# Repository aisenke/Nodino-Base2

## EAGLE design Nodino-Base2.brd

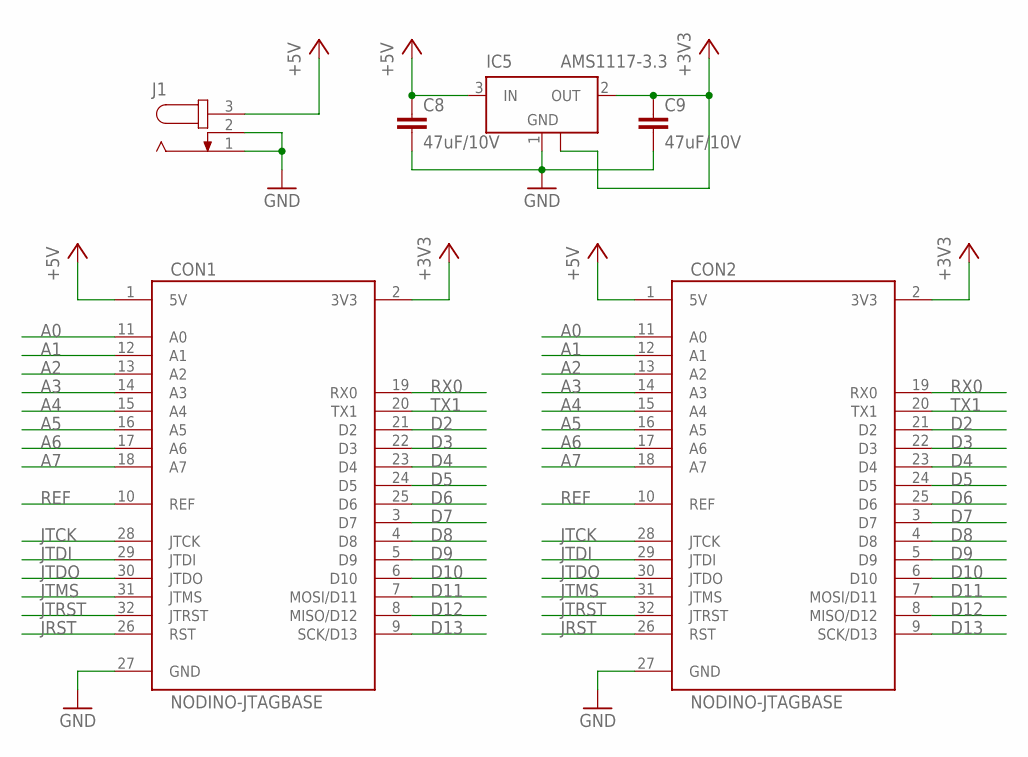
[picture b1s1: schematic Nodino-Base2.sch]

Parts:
C8, C9: 47uF/10V; C3225
CON1, CON2: NODINO-JTAGBASE; NODINO-JTAG-BASE
IC5: AMS1117-3.3; SOT223
J1: JACK-PLUG0; SPC4077

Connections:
+3V3: C9.1, CON1.2 (3V3), CON2.2 (3V3), IC5.2 (OUT), IC5.4 (GND)
+5V: C8.1, CON1.1 (5V), CON2.1 (5V), IC5.3 (IN), J1.3
A0: CON1.11 (A0), CON2.11 (A0)
A1: CON1.12 (A1), CON2.12 (A1)
A2: CON1.13 (A2), CON2.13 (A2)
A3: CON1.14 (A3), CON2.14 (A3)
A4: CON1.15 (A4), CON2.15 (A4)
A5: CON1.16 (A5), CON2.16 (A5)
A6: CON1.17 (A6), CON2.17 (A6)
A7: CON1.18 (A7), CON2.18 (A7)
D2: CON1.21 (D2), CON2.21 (D2)
D3: CON1.22 (D3), CON2.22 (D3)
D4: CON1.23 (D4), CON2.23 (D4)
D5: CON1.24 (D5), CON2.24 (D5)
D6: CON1.25 (D6), CON2.25 (D6)
D7: CON1.3 (D7), CON2.3 (D7)
D8: CON1.4 (D8), CON2.4 (D8)
D9: CON1.5 (D9), CON2.5 (D9)
D10: CON1.6 (D10), CON2.6 (D10)
D11: CON1.7 (MOSI/D11), CON2.7 (MOSI/D11)
D12: CON1.8 (MISO/D12), CON2.8 (MISO/D12)
D13: CON1.9 (SCK/D13), CON2.9 (SCK/D13)
GND: C8.2, C9.2, CON1.27 (GND), CON2.27 (GND), IC5.1 (GND), J1.1, J1.2
JRST: CON1.26 (RST), CON2.26 (RST)
JTCK: CON1.28 (JTCK), CON2.28 (JTCK)
JTDI: CON1.29 (JTDI), CON2.29 (JTDI)
JTDO: CON1.30 (JTDO), CON2.30 (JTDO)
JTMS: CON1.31 (JTMS), CON2.31 (JTMS)
JTRST: CON1.32 (JTRST), CON2.32 (JTRST)
REF: CON1.10 (REF), CON2.10 (REF)
RX0: CON1.19 (RX0), CON2.19 (RX0)
TX1: CON1.20 (TX1), CON2.20 (TX1)

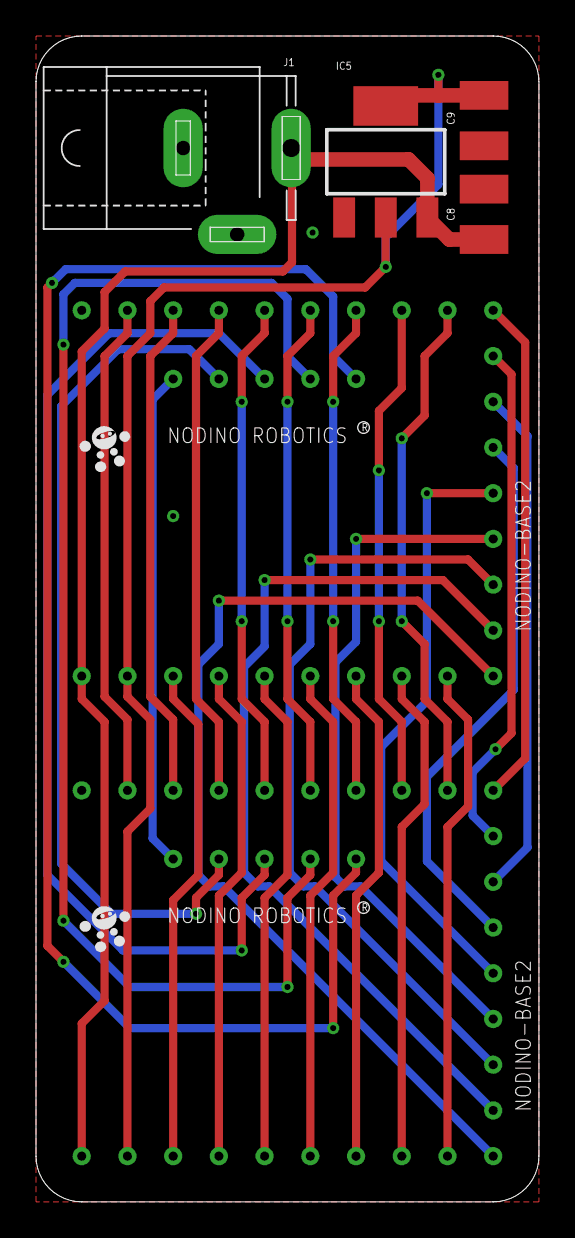
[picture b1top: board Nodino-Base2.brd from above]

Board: 2 copper layers, 27.9 x 64.8 mm, 6 parts (0 on the bottom side), 32 nets.

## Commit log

2014-03-28 final version
2014-04-12 minor fix
2014-04-12 added a version without power adapter
